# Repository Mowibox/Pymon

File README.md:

# Pymon

Game project developed with OpenCV and STM32 for the Image & Virtual Reality Workshop.

## About the game

Pymon is a Python derivative of the game Simon where the objective is to memorize and reproduce sequences of random colors.

The unique aspect of Pymon is that the game interface is created using the player's computer camera, and color selection is done directly on the screen by hand detection.

Serial communication is established with the game box to retrieve player inputs.

## How to play?

Clone this repository to your computer:

```bash
git clone https://github.com/Mowibox/Pymon.git
```

Connect the game device to your computer; a sound sequence should play if everything is working correctly.

Open the `main.py` file in the Python folder and install the libraries by using the requirements file:

```bash
pip install -r requirements.txt
```

Have fun!

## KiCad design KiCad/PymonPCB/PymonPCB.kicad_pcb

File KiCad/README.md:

# KiCad Pymon PCB

The electronic board of the Pymon game rests in this folder.

The PCB contains 4 LEDs and their associated resistors, a buzzer, and two female connectors for the NUCLEO F303K8 board.

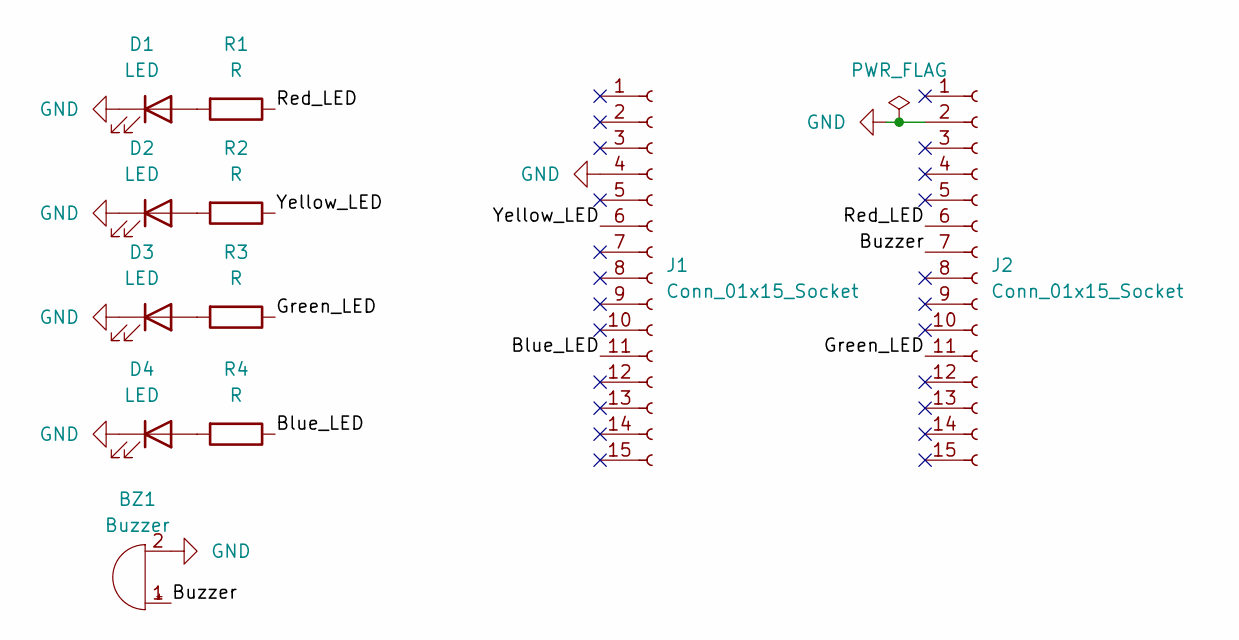
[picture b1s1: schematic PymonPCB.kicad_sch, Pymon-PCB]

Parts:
BZ1: Buzzer; MagneticBuzzer_ProSignal_ABT-410-RC
D1, D2, D3, D4: LED; LED_D5.0mm_Clear
J1, J2: Conn_01x15_Socket; PinSocket_1x15_P2.54mm_Vertical
R1, R2, R3, R4: R; R_0603_1608Metric

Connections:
/Blue_LED: J1.11, R4.1
/Buzzer: BZ1.1 (-), J2.7
/Green_LED: J2.11, R3.1
/Red_LED: J2.6, R1.1
/Yellow_LED: J1.6, R2.1
GND: BZ1.2 (+), D1.1 (K), D2.1 (K), D3.1 (K), D4.1 (K), J1.4, J2.2
unnamed: D1.2 (A), R1.2
unnamed: D2.2 (A), R2.2
unnamed: D3.2 (A), R3.2
unnamed: D4.2 (A), R4.2

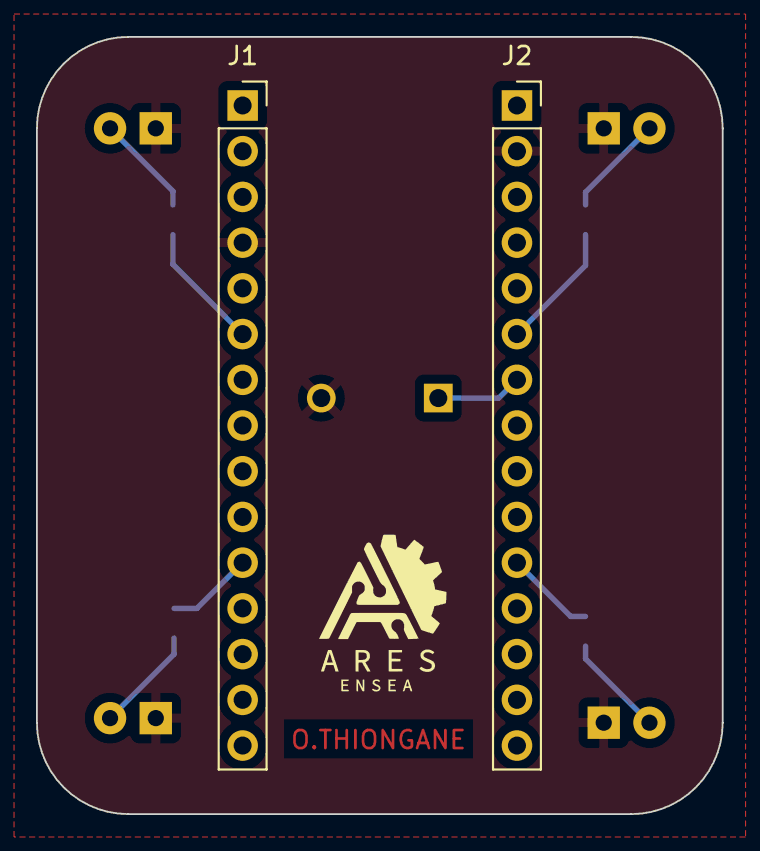
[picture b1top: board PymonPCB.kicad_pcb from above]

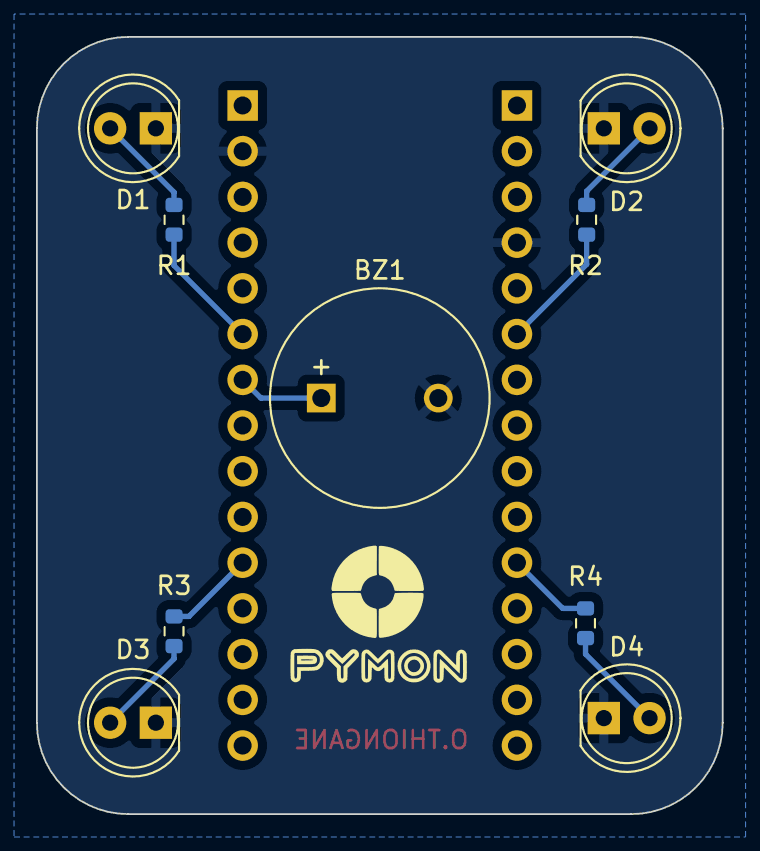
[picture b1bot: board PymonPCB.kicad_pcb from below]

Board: 2 copper layers, 38.1 x 43.2 mm, 11 parts (9 on the bottom side), 10 nets.

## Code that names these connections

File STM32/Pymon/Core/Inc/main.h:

/* USER CODE BEGIN Header */
/**
  ******************************************************************************
  * @file           : main.h
  * @brief          : Header for main.c file.
  *                   This file contains the common defines of the application.
  ******************************************************************************
  * @attention
  *
  * Copyright (c) 2024 STMicroelectronics.
  * All rights reserved.
  *
  * This software is licensed under terms that can be found in the LICENSE file
  * in the root directory of this software component.
  * If no LICENSE file comes with this software, it is provided AS-IS.
  *
  ******************************************************************************
  */
/* USER CODE END Header */

/* Define to prevent recursive inclusion -------------------------------------*/
#ifndef __MAIN_H
#define __MAIN_H

#ifdef __cplusplus
extern "C" {
#endif

/* Includes ------------------------------------------------------------------*/
#include "stm32f3xx_hal.h"

/* Private includes ----------------------------------------------------------*/
/* USER CODE BEGIN Includes */

/* USER CODE END Includes */

/* Exported types ------------------------------------------------------------*/
/* USER CODE BEGIN ET */

/* USER CODE END ET */

/* Exported constants --------------------------------------------------------*/
/* USER CODE BEGIN EC */

/* USER CODE END EC */

/* Exported macro ------------------------------------------------------------*/
/* USER CODE BEGIN EM */

/* USER CODE END EM */

void HAL_TIM_MspPostInit(TIM_HandleTypeDef *htim);

/* Exported functions prototypes ---------------------------------------------*/
void Error_Handler(void);

/* USER CODE BEGIN EFP */

/* USER CODE END EFP */

/* Private defines -----------------------------------------------------------*/
#define MCO_Pin GPIO_PIN_0
#define MCO_GPIO_Port GPIOF
#define Blue_LED_Pin GPIO_PIN_1
#define Blue_LED_GPIO_Port GPIOF
#define Green_LED_Pin GPIO_PIN_1
#define Green_LED_GPIO_Port GPIOA
#define VCP_TX_Pin GPIO_PIN_2
#define VCP_TX_GPIO_Port GPIOA
#define Red_LED_Pin GPIO_PIN_7
#define Red_LED_GPIO_Port GPIOA
#define Yellow_LED_Pin GPIO_PIN_0
#define Yellow_LED_GPIO_Port GPIOB
#define BUZZER_Pin GPIO_PIN_8
#define BUZZER_GPIO_Port GPIOA
#define SWDIO_Pin GPIO_PIN_13
#define SWDIO_GPIO_Port GPIOA
#define SWCLK_Pin GPIO_PIN_14
#define SWCLK_GPIO_Port GPIOA
#define VCP_RX_Pin GPIO_PIN_15
#define VCP_RX_GPIO_Port GPIOA

/* USER CODE BEGIN Private defines */

/* USER CODE END Private defines */

#ifdef __cplusplus
}
#endif

#endif /* __MAIN_H */

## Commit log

2024-03-17 Game first version
2024-03-17 First update
2024-03-18 PCB update & Code correction
2024-03-18 Adding Settings buttons
2024-03-26 COM Port update & LED update
2024-03-30 Adding corrections
2024-03-31 Score Button Update
2024-03-31 Renaming Led Pins
2024-03-31 README.md Updates
2024-03-31 Moving README.md
2024-03-31 Adding .gitignore
2024-03-31 Cleaning
2024-03-31 Img update
2024-04-01 Minor correction
2024-04-03 Image update
2024-04-03 Adding images
2024-04-07 Header update
2025-01-09 Update code for Julie
2025-01-09 Update for Julie
2026-02-02 Update README.md and images
2026-02-02 remove png from .gitignore
